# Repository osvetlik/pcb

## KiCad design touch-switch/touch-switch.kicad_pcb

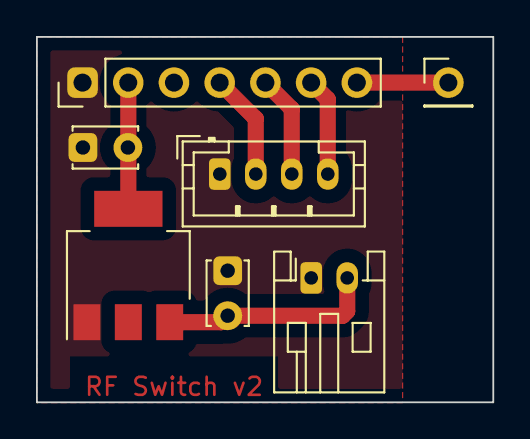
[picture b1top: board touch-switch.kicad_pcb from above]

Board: 2 copper layers, 25.4 x 20.3 mm, 5 parts (0 on the bottom side), 4 nets.

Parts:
AMS1117-3.3: AMS1117-3.3; SOT-223-3_TabPin2
Antenna: Conn_01x01; PinHeader_1x01_P2.54mm_Vertical
C1, C2: C; C_Disc_D3.4mm_W2.1mm_P2.50mm
RFTransmitter1: Conn_01x07; PinHeader_1x07_P2.54mm_Vertical

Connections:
+3.3V: AMS1117-3.3.2 (VO), C2.1, RFTransmitter1.2
+12V: AMS1117-3.3.3 (VI), C1.1
Earth: AMS1117-3.3.1 (GND), C1.2, C2.2, RFTransmitter1.1
unnamed: Antenna.1, RFTransmitter1.7

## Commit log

2023-02-25 Touch switch PCB
